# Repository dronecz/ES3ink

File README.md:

### ES3ink is a board designed to control e-ink displays. 

This repo holds HW and SW (to be done) information for this board.

It can be used with Arduino or [CircuitPython](https://github.com/dronecz/circuitpython).

You can view [schematic](https://kicanvas.org/?github=https%3A%2F%2Fgithub.com%2Fdronecz%2FES3ink%2Fblob%2Fmain%2FHW%2FES3ink.kicad_sch) or [board layout](https://kicanvas.org/?github=https%3A%2F%2Fgithub.com%2Fdronecz%2FES3ink%2Fblob%2Fmain%2FHW%2FES3ink.kicad_pcb) in [KiCanvas](https://kicanvas.org/).

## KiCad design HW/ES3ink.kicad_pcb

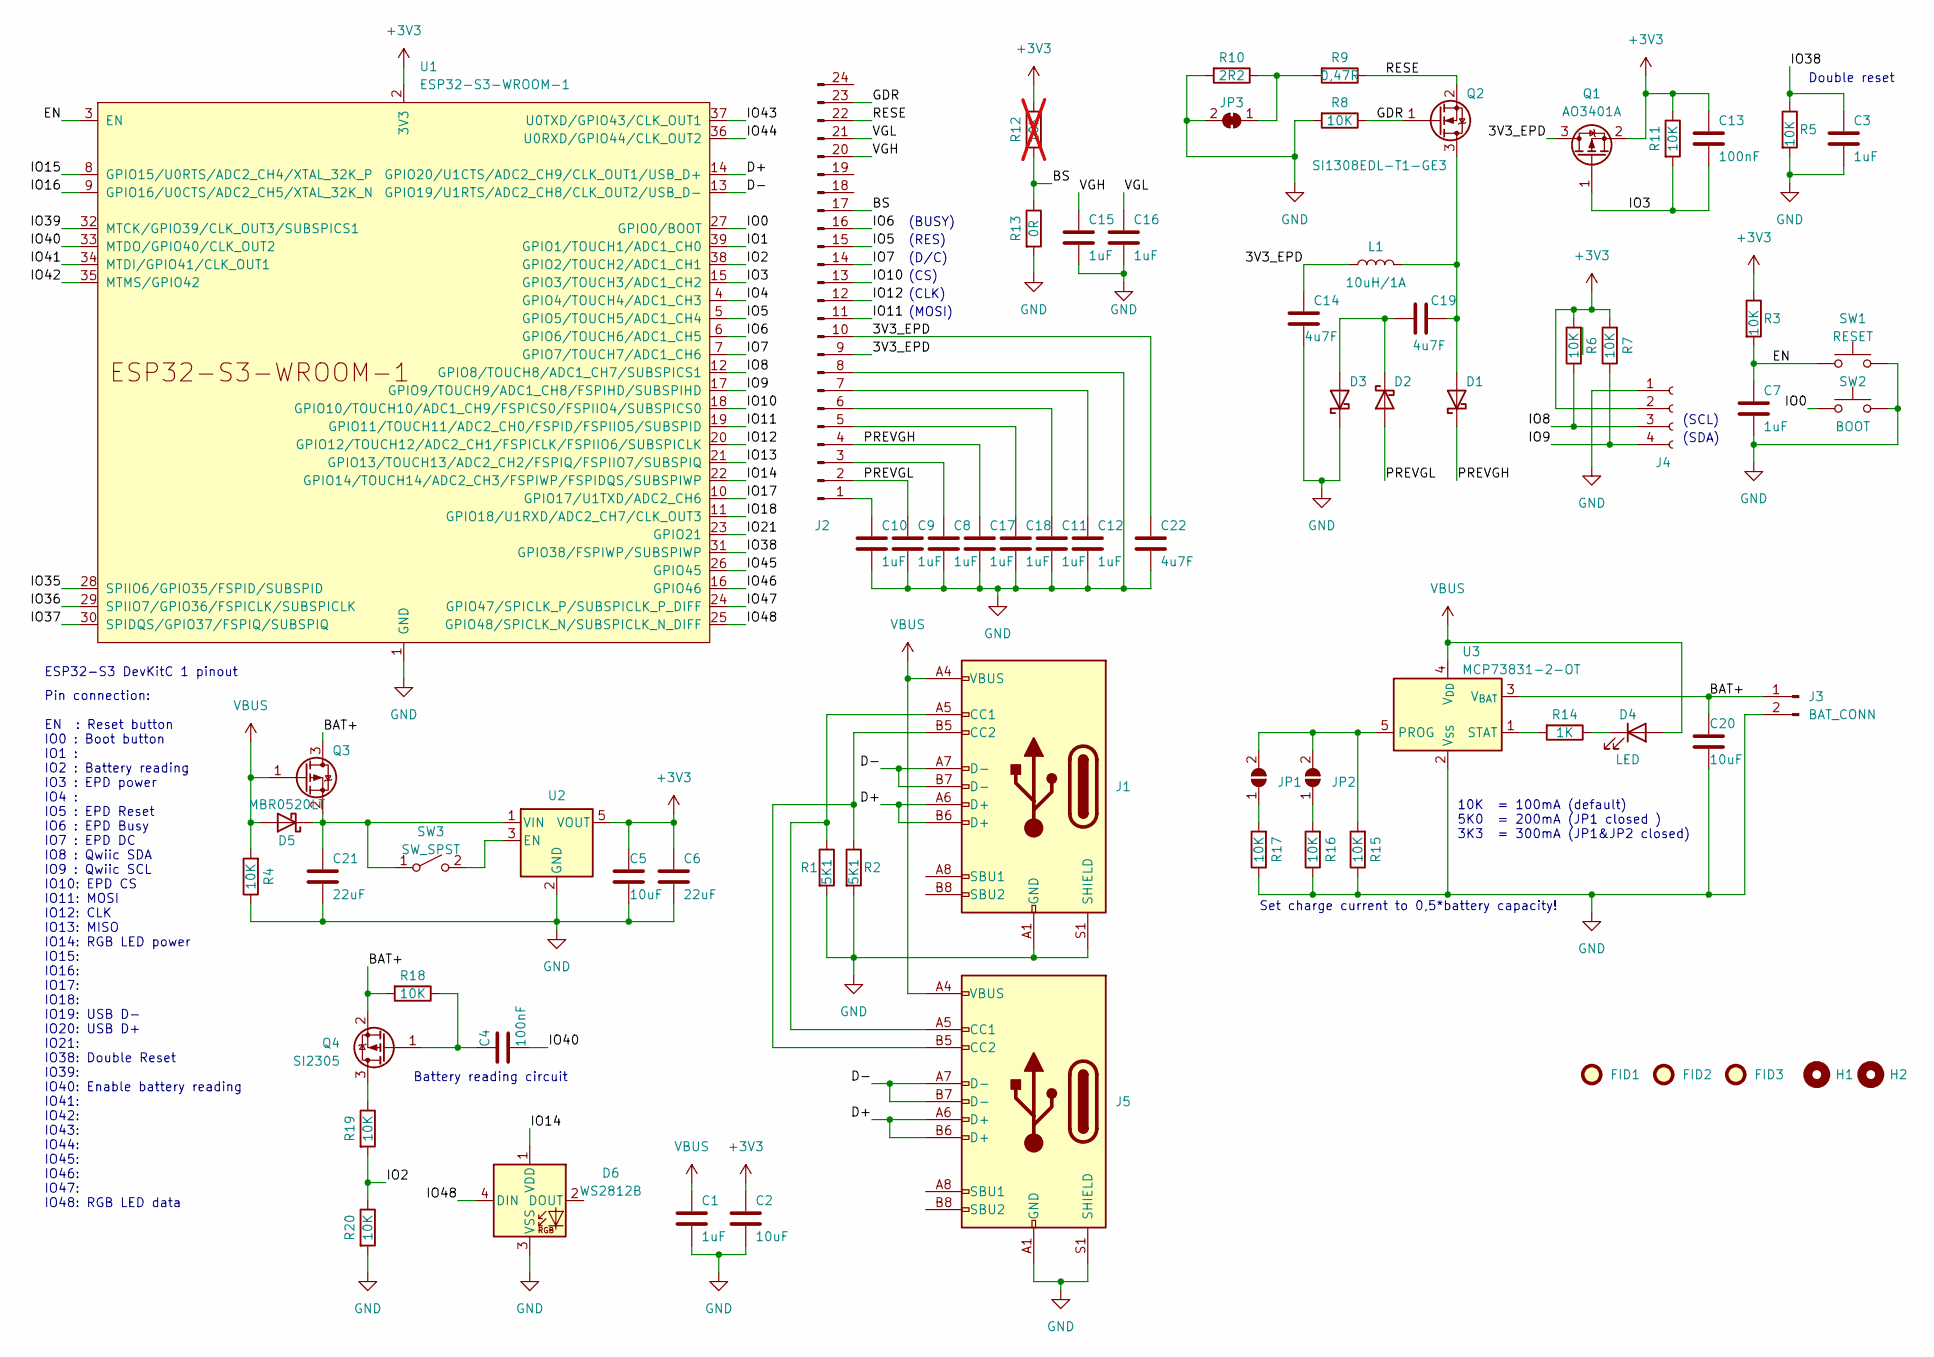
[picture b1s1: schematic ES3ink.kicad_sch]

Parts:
C1, C3, C7, C8, C9, C10, C11, C12, C15, C16, C17, C18: 1uF; C_0805_2012Metric
C2, C5, C20: 10uF; C_0805_2012Metric
C4, C13: 100nF; C_0805_2012Metric
C6, C21: 22uF; C_0805_2012Metric
C14, C19, C22: 4u7F; C_0805_2012Metric
D1, D2, D3: MBR0530; D_SOD-123
D4: LED; D_0805_2012Metric
D5: MBR0520LT; D_SOD-123
D6: WS2812B; LED_WS2812B-2020_PLCC4_2.0x2.0mm
FID1, FID2, FID3: Fiducial; Fiducial_0.75mm_Mask1.5mm
H1, H2: MountingHole; MountingHole_3.2mm_M3_DIN965_Pad
J1: USB_C_Receptacle_USB2.0; USB_C_Receptacle_HRO_TYPE-C-31-M-12
J2: Conn_01x24_Pin; GCT_FFC2B28-24-G
J3: BAT_CONN; JST_PH_S2B-PH-SM4-TB_1x02-1MP_P2.00mm_Horizontal
J4: Conn_01x04_Socket; JST_SH_SM04B-SRSS-TB_1x04-1MP_P1.00mm_Horizontal
J5: USB_C_Receptacle_USB2.0; USB_C_Receptacle_HRO_TYPE-C-31-M-15
JP1, JP2: SolderJumper_2_Open; SolderJumper-2_P1.3mm_Open_TrianglePad1.0x1.5mm
JP3: SolderJumper_2_Open; SolderJumper-2_P1.3mm_Bridged_RoundedPad1.0x1.5mm
L1: 10uH/1A; L_1812_4532Metric; Mouser LQH43PN100M26L
Q1: AO3401A; SOT-23
Q2: SI1308EDL-T1-GE3; SOT-323_SC-70
Q3: DMP2045U-7; SOT-23
Q4: SI2305; SOT-23
R1, R2: 5K1; R_0805_2012Metric
R3, R4, R5, R6, R7, R8, R11, R15, R16, R17, R18, R19, R20: 10K; R_0805_2012Metric
R9: 0,47R; R_0805_2012Metric
R10: 2R2; R_0805_2012Metric
R12: 10K; R_0805_2012Metric; not fitted
R13: 0R; R_0805_2012Metric
R14: 1K; R_0805_2012Metric
SW1: RESET; SW_Push_1P1T_NO_CK_KMR2
SW2: BOOT; SW_Push_1P1T_NO_CK_KMR2
SW3: SW_SPST; JS202011JCQN
U1: ESP32-S3-WROOM-1
U2: AP2112K-3.3; SOT-23-5
U3: MCP73831-2-OT; SOT-23-5

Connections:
+3V3: C2.1, C5.1, C6.1, C13.1, J4.2, Q1.2 (S), R3.1, R6.2, R7.2, R11.1, R12.1, U1.2 (3V3), U2.5 (VOUT)
/3V3_EPD: C14.1, C22.1, J2.9, J2.10, L1.1, Q1.3 (D)
/BAT+: C20.1, J3.1, Q3.3 (D), Q4.2 (S), R18.2, U3.3 (V_{BAT})
/BS: J2.17, R12.2, R13.1
/D+: J1.A6 (D+), J1.B6 (D+), J5.A6 (D+), J5.B6 (D+), U1.14 (GPIO20/U1CTS/ADC2_CH9/CLK_OUT1/USB_D+)
/D-: J1.A7 (D-), J1.B7 (D-), J5.A7 (D-), J5.B7 (D-), U1.13 (GPIO19/U1RTS/ADC2_CH8/CLK_OUT2/USB_D-)
/EN: C7.1, R3.2, SW1.1, U1.3 (EN)
/GDR: J2.23, Q2.1 (G), R8.1
/IO0: SW2.1, U1.27 (GPIO0/BOOT)
/IO1: U1.39 (GPIO1/TOUCH1/ADC1_CH0)
/IO2: R19.2, R20.1, U1.38 (GPIO2/TOUCH2/ADC1_CH1)
/IO3: C13.2, Q1.1 (G), R11.2, U1.15 (GPIO3/TOUCH3/ADC1_CH2)
/IO4: U1.4 (GPIO4/TOUCH4/ADC1_CH3)
/IO5: J2.15, U1.5 (GPIO5/TOUCH5/ADC1_CH4)
/IO6: J2.16, U1.6 (GPIO6/TOUCH6/ADC1_CH5)
/IO7: J2.14, U1.7 (GPIO7/TOUCH7/ADC1_CH6)
/IO8: J4.3, R6.1, U1.12 (GPIO8/TOUCH8/ADC1_CH7/SUBSPICS1)
/IO9: J4.4, R7.1, U1.17 (GPIO9/TOUCH9/ADC1_CH8/FSPIHD/SUBSPIHD)
/IO10: J2.13, U1.18 (GPIO10/TOUCH10/ADC1_CH9/FSPICS0/FSPIIO4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)
/IO11: J2.11, U1.19 (GPIO11/TOUCH11/ADC2_CH0/FSPID/FSPIIO5/S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)
/IO12: J2.12, U1.20 (GPIO12/TOUCH12/ADC2_CH1/FSPICLK/FSPIIO6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)
/IO13: U1.21 (GPIO13/TOUCH13/ADC2_CH2/FSPIQ/FSPIIO7/S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)
/IO14: D6.1 (VDD), U1.22 (GPIO14/TOUCH14/ADC2_CH3/FSPIWP/FSPIDQS/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)
/IO15: U1.8 (GPIO15/U0RTS/ADC2_CH4/XTAL_32K_P)
/IO16: U1.9 (GPIO16/U0CTS/ADC2_CH5/XTAL_32K_N)
/IO17: U1.10 (GPIO17/U1TXD/ADC2_CH6)
/IO18: U1.11 (GPIO18/U1RXD/ADC2_CH7/CLK_OUT3)
/IO21: U1.23 (GPIO21)
/IO35: U1.28 (SPIIO6/GPIO35/FSPID/SUBSPID)
/IO36: U1.29 (SPIIO7/GPIO36/FSPICLK/SUBSPICLK)
/IO37: U1.30 (SPIDQS/GPIO37/FSPIQ/SUBSPIQ)
/IO38: C3.1, R5.1, U1.31 (GPIO38/FSPIWP/SUBSPIWP)
/IO39: U1.32 (MTCK/GPIO39/CLK_OUT3/SUBSPICS1)
/IO40: C4.2, U1.33 (MTDO/GPIO40/CLK_OUT2)
/IO41: U1.34 (MTDI/GPIO41/CLK_OUT1)
/IO42: U1.35 (MTMS/GPIO42)
/IO43: U1.37 (U0TXD/GPIO43/CLK_OUT1)
/IO44: U1.36 (U0RXD/GPIO44/CLK_OUT2)
/IO45: U1.26 (GPIO45)
/IO46: U1.16 (GPIO46)
/IO47: U1.24 (GPIO47/SPICLK_P/SUBSPICLK_P_DIFF)
/IO48: D6.4 (DIN), U1.25 (GPIO48/SPICLK_N/SUBSPICLK_N_DIFF)
/PREVGH: C17.1, D1.1 (K), J2.4
/PREVGL: C9.1, D2.2 (A), J2.2
/RESE: J2.22, Q2.2 (S), R9.1
/VGH: C15.1, J2.20
/VGL: C16.1, J2.21
GND: C1.2, C2.2, C3.2, C5.2, C6.2, C7.2, C8.2, C9.2, C10.2, C11.2, C12.2, C14.2, C15.2, C16.2, C17.2, C18.2, C20.2, C21.2, C22.2, D3.1 (K), D6.3 (VSS), J1.A1 (GND), J1.A12 (GND), J1.B1 (GND), J1.B12 (GND), J1.S1 (SHIELD), J2.8, J3.2, J4.1, J5.A1 (GND), J5.A12 (GND), J5.B1 (GND), J5.B12 (GND), J5.S1 (SHIELD), JP3.2 (B), R1.2, R2.2, R4.1, R5.2, R8.2, R10.2, R13.2, R15.1, R16.1, R17.1, R20.2, SW1.2, SW2.2, U1.1 (GND), U1.40 (GND), U1.41 (GND), U2.2 (GND), U3.2 (V_{SS})
unnamed: C19.1, D1.2 (A), L1.2, Q2.3 (D)
unnamed: C19.2, D2.1 (K), D3.2 (A)
unnamed: D4.1 (K), R14.1
unnamed: C21.1, D5.1 (K), Q3.2 (S), SW3.1 (A), U2.1 (VIN)
unnamed: J1.A5 (CC1), J5.A5 (CC1), R1.1
unnamed: J1.B5 (CC2), J5.B5 (CC2), R2.1
unnamed: C10.1, J2.1
unnamed: C8.1, J2.3
unnamed: C18.1, J2.5
unnamed: C11.1, J2.6
unnamed: C12.1, J2.7
unnamed: JP1.1 (A), R17.2
unnamed: JP1.2 (B), JP2.2 (B), R15.2, U3.5 (PROG)
unnamed: JP2.1 (A), R16.2
unnamed: JP3.1 (A), R9.2, R10.1
unnamed: Q4.3 (D), R19.1
unnamed: C4.1, Q4.1 (G), R18.1
unnamed: SW3.2 (B), U2.3 (EN)
unnamed: R14.2, U3.1 (STAT)
VBUS: C1.1, D4.2 (A), D5.2 (A), J1.A4 (VBUS), J1.A9 (VBUS), J1.B4 (VBUS), J1.B9 (VBUS), J5.A4 (VBUS), J5.A9 (VBUS), J5.B4 (VBUS), J5.B9 (VBUS), Q3.1 (G), R4.2, U3.4 (V_{DD})

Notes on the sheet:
(RES)
(D/C)
Battery reading circuit
(SCL)
(CLK)
(SDA)
10K = 100mA (default) 5K0 = 200mA (JP1 closed ) 3K3 = 300mA (JP1&JP2 closed)
(BUSY)
Double reset
(MOSI)
Set charge current to 0,5*battery capacity!
Pin connection: EN : Reset button IO0 : Boot button IO1 : IO2 : Battery reading IO3 : EPD power IO4 : IO5 : EPD Reset IO6 : EPD Busy IO7 : EPD DC IO8 : Qwiic SDA IO9 : Qwiic SCL IO10: EPD CS IO11: MOSI IO12: CLK IO13: MISO IO14: RGB LED power IO15: IO16: IO17: IO18: IO19: USB D- IO20: USB D+ IO21: 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
(CS)
ESP32-S3 DevKitC 1 pinout

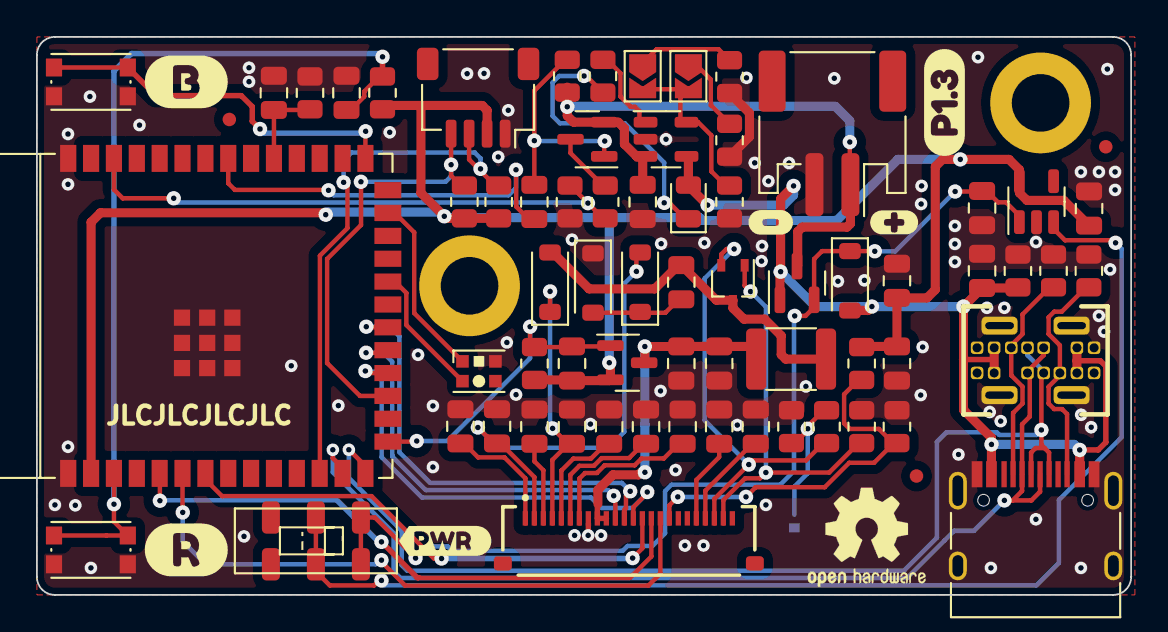
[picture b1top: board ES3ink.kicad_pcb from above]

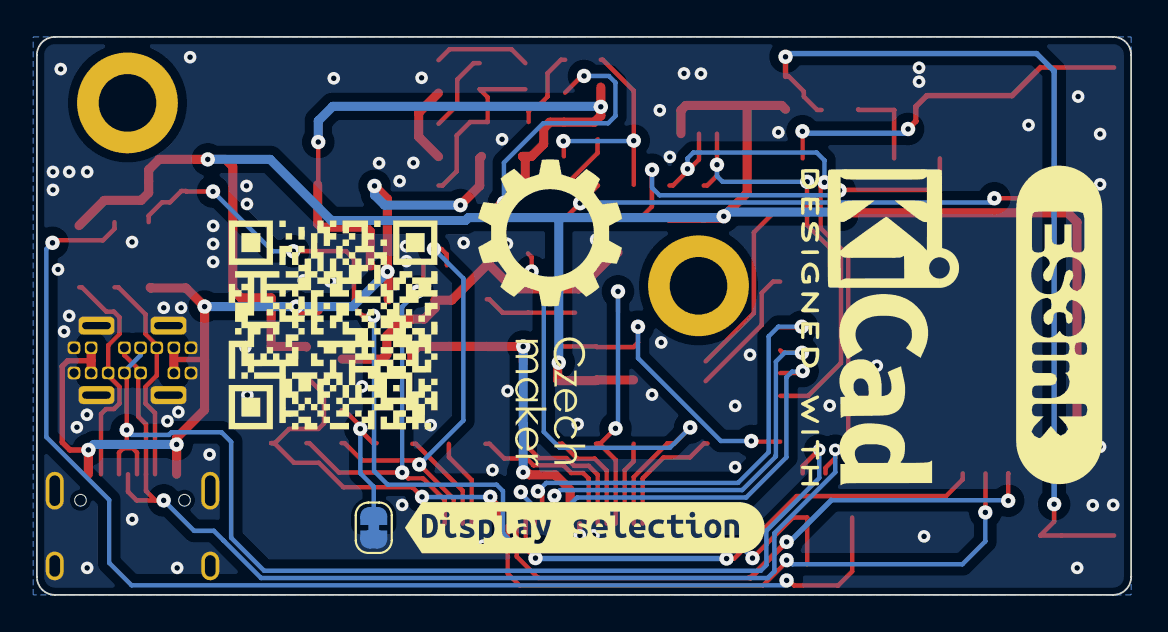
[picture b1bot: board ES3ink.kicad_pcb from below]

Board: 2 copper layers, 60.8 x 31.0 mm, 80 parts (3 on the bottom side), 49 nets.

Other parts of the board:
kibuzzard-659DC4DE: G***; kibuzzard-659DC4DE
kibuzzard-6951B36D: G***; kibuzzard-6951B36D
kibuzzard-6951C433: G***; kibuzzard-6951C433
kibuzzard-64921EEB: G***; kibuzzard-64921EEB
kibuzzard-64921EFB: G***; kibuzzard-64921EFB
kibuzzard-65272A96: G***; kibuzzard-65272A96
kibuzzard-649216A2: G***; kibuzzard-649216A2
kibuzzard-649216B3: G***; kibuzzard-649216B3

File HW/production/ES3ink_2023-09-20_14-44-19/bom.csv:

Designator,Footprint,Quantity,Value,LCSC Part #
"C1, C10, C11, C12, C15, C16, C17, C18, C3, C7, C8, C9",0805,12,1uF,
"C12.3546, C20, C4, C5",0805,4,10uF,
C13,0805,1,100nF,
"C14, C19, C22",0805,3,4u7F,
"C21, C6",0805,2,22uF,
"D1, D2, D3, D5",D_SOD-123,4,MBR0520LT,
D4,0805,1,LED,
D6,LED_WS2812B-2020_PLCC4_2.0x2.0mm,1,WS2812B,
"H1, H2",MountingHole_3.2mm_M3_DIN965_Pad,2,MountingHole,
J1,USB_C_Receptacle_HRO_TYPE-C-31-M-12,1,USB_C_Receptacle_USB2.0,
J2,TE_2-1734839-4_1x24-1MP_P0.5mm_Horizontal,1,Conn_01x24_Pin,
J3,JST_PH_S2B-PH-SM4-TB_1x02-1MP_P2.00mm_Horizontal,1,Conn_01x02_Pin,
J4,JST_SH_SM04B-SRSS-TB_1x04-1MP_P1.00mm_Horizontal,1,Conn_01x04_Socket,
J5,USB_C_Receptacle_HRO_TYPE-C-31-M-15,1,USB_C_Receptacle_USB2.0,
"JP1, JP2, JP3",SolderJumper-2_P1.3mm_Open_TrianglePad1.0x1.5mm,3,SolderJumper_2_Open,
L1,1812,1,10uH/1A,
"Q1, Q3",SOT-23,2,DMG3415U-7,
Q2,SOT-23,1,SI1308EDL-T1-GE3,
Q4,SOT-23,1,SI2305,
"R1, R2",0805,2,5K1,
R10,0805,1,2R2,
"R11, R15, R16, R17, R18, R19, R20, R3, R4, R5, R6, R7, R8",0805,13,10K,
R12,0805,1,10K,DNP
R13,0805,1,0R,
R14,0805,1,1K,
R8.8456,0805,1,"0,47R",
SW1,SW_Push_1P1T_NO_CK_KMR2,1,RESET,
SW2,SW_Push_1P1T_NO_CK_KMR2,1,BOOT,
SW3,JS202011JCQN,1,SW_SPST,
U1,ESP32-S3-WROOM-2,1,ESP32-S3-WROOM-2,
U2,SOT-23-5,1,AP2112K-3.3,
U3,SOT-23-5,1,MCP73831-2-OT,

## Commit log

2023-07-11 HW design files upload
2023-07-18 Backlink to CADLAB.io has been added.
2023-07-18 Update
    - renamed files
    - changed schematic to follow Waveshare e-Paper driver HAT
2023-07-18 Removed old files
2023-09-20 Component update
2023-09-20 Version 2.5 upload
2023-09-20 Layout change & production files
2023-09-29 PCB size increase so it can be manufactured with V-cuts
2023-10-03 Update component values
2023-10-07 Update
    - pin change to match ESP32-S3 DevKitC 1
    - revision change to P1.0 (production)
2023-10-07 R18 value change
2023-10-07 Update
    - fix I2C pin at Qwiic connector
    - fix SPI CLK pin for EPD
2023-10-24 Update
    - component value change
    - FPC connector changed to double side connection
    - version increase to 1.1
2023-11-15 Add title in schematic
2024-01-09 Update to P1.2
    - changed e-ink pwr pin to IO3
    - unified reference text values
    - add link to view design in KiCanvas
    - version increment to P1.2
2024-01-09 Update ES3ink.kicad_pcb
    - disable visibility of some values
2024-05-27 Update
    - changed format to KiCad 8
    - changed some tracks
    - add JP3 label
    - add OHW logo
2025-12-29 Update
    - upgrade to KiCad 9
    - changed U1 from ESP32-S3-WROOM-2 to WROOM-1
    - added 3D models to project
    - added fiducials
    - changed routing of the board
